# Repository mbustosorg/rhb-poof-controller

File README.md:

Red Hot Beverly Poof Controller
===============================

The Red Hot Beverly's poof button panel: CircuitPython on a Waveshare
ESP32-S3-POE-ETH at `192.168.1.15`, wired and powered over PoE.

1. Sends `/poof 1.0` on press and `/poof 0.0` on release to every listener.
2. Shows accumulator pressure (`/pressure`) on the left two digits.
3. Shows water bath temperature (`/temperature`) on the right two digits,
   blinking while `/water_heater` is 1.

OSC
---

| Direction | Address | Value | Producer / consumers |
| --- | --- | --- | --- |
| out | `/poof` | `1.0` pressed, `0.0` released | Every address in `CLIENTS`, including the body display |
| in | `/pressure` | psi, float | rhb-sensor-monitor |
| in | `/temperature` | degrees F, float | rhb-water-heater |
| in | `/water_heater` | `1.0` heating, `0.0` off | rhb-water-heater |

All on UDP 8888, except the body display at `192.168.1.3:10002`.

- `/poof` is a level, not a count: the release is sent three times, 50 ms
  apart, in case one is lost.
- At boot it sends `/poof 0.0`; a button held at power up must be released
  first.
- Edges are debounced 20 ms (`DEBOUNCE_MS`) and scanned in the background, so
  one that arrives during a send is late, not lost.
- An unreachable listener is skipped for 2, 4, 8 ... up to 60 s, since each
  failed send blocks for up to 0.5 s.
- A readout shows `--` before its first value and after 15 s without one.
  Values are rounded; above 99 shows `99`, below 0 shows `--`.

Hardware
--------

See [HARDWARE.md](HARDWARE.md) for the wiring and [kicad/](kicad/README.md) for the board.

| Part | ESP32-S3-ETH pin |
| --- | --- |
| HT16K33 display, I2C `0x70` | SDA IO39, SCL IO38 |
| Button, through a PC817 | IO40, internal pull-up, low = pressed |
| Onboard RGB LED | IO21, red while pressed |
| W5500 Ethernet | IO9-IO14, on the board |

The temperature pair blinks in software (`blink_loop`), since the HT16K33's
blink would flash all four digits.

`rhb_utils.py` and the OSC receive path (`poll_osc`, `start_osc`) are
rhb-water-heater's, with its W5500 fixes.  Keep the two in step.

Configuration
-------------

`config_rhb.json` is gitignored; copy `config_rhb.json.example`.

| Key | Default | Meaning |
| --- | --- | --- |
| `IP` | | Static address; no DHCP on the rig |
| `CLIENTS` | every rig listener | Who hears `/poof`.  `host` for port 8888, `host:port` otherwise |
| `POOF_PIN` | `"IO40"` | Button input, a `board` pin name |
| `DEBOUNCE_MS` | `20` | How long an edge must hold |
| `DISPLAY` | `112` (0x70) | Display I2C address, decimal since JSON has no hex |

Deploying
---------

Flash CircuitPython for the Waveshare ESP32-S3-ETH, then copy to `CIRCUITPY`
over USB-C:

- `code.py`, `rhb_utils.py`, `config_rhb.json`
- Into `lib/`, from the Adafruit bundle: `adafruit_ht16k33`,
  `adafruit_bus_device`, `adafruit_wiznet5k`, `adafruit_ticks`, `asyncio`,
  and optionally `neopixel`
- `microosc`, from the Community bundle

Console: `/dev/cu.usbmodem<UID>` (`cu.*`, not `tty.*`).  The display flashes
`[[]]` until the link is up, then `-- --` until data arrives.

Testing
-------

`test_osc.py` sends random readings every 5 s and prints each `/poof`.  Run
it from an address in `CLIENTS`:

    python3 test_osc.py --ip 192.168.1.15

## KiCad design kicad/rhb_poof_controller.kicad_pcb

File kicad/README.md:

Poof Controller Board
=====================

Two layer, 74 x 43 mm carrier for the circuit in [HARDWARE.md](../HARDWARE.md).
Parts: [bom.csv](bom.csv).

- **U2** mounts top face up; its RJ45 / USB-C end overhangs the left edge by
  2 mm.
- **R1, D1 and U1** sit under U2, between its header rows.  Fit them
  before the sockets, and keep them under 4.5 mm tall.
- **J1** takes the button wire, after the inline fuse at the supply, and the
  supply's negative.
- The bottom ground pour leaves out the 12V side, J1, R1, D1 and the
  PC817's LED pins, except for a strip along U2's pin 1-20 row.

The U2 footprint comes from Waveshare's dimension drawing.  **Check it against
a real board before ordering**: lay the module on a 1:1 print and see that
pin 1 lands on the square pad.  Also check that R1, D1 and U1 clear the
W5500, TF slot and USB-C on the module's underside once it's in its sockets.

Regenerating
------------

Edit the scripts, not the KiCad files, then run `./build.sh`.  Routing needs
Java 17+ and `~/tools/freerouting-1.9.jar`.

Expected warnings:

| Warning | Why |
| --- | --- |
| `lib_symbol_issues` | Symbols live only in the schematic |
| `extra_footprint` | Mounting holes aren't in the schematic |
| `silk_edge_clearance` | U2's outline runs past the board edge |

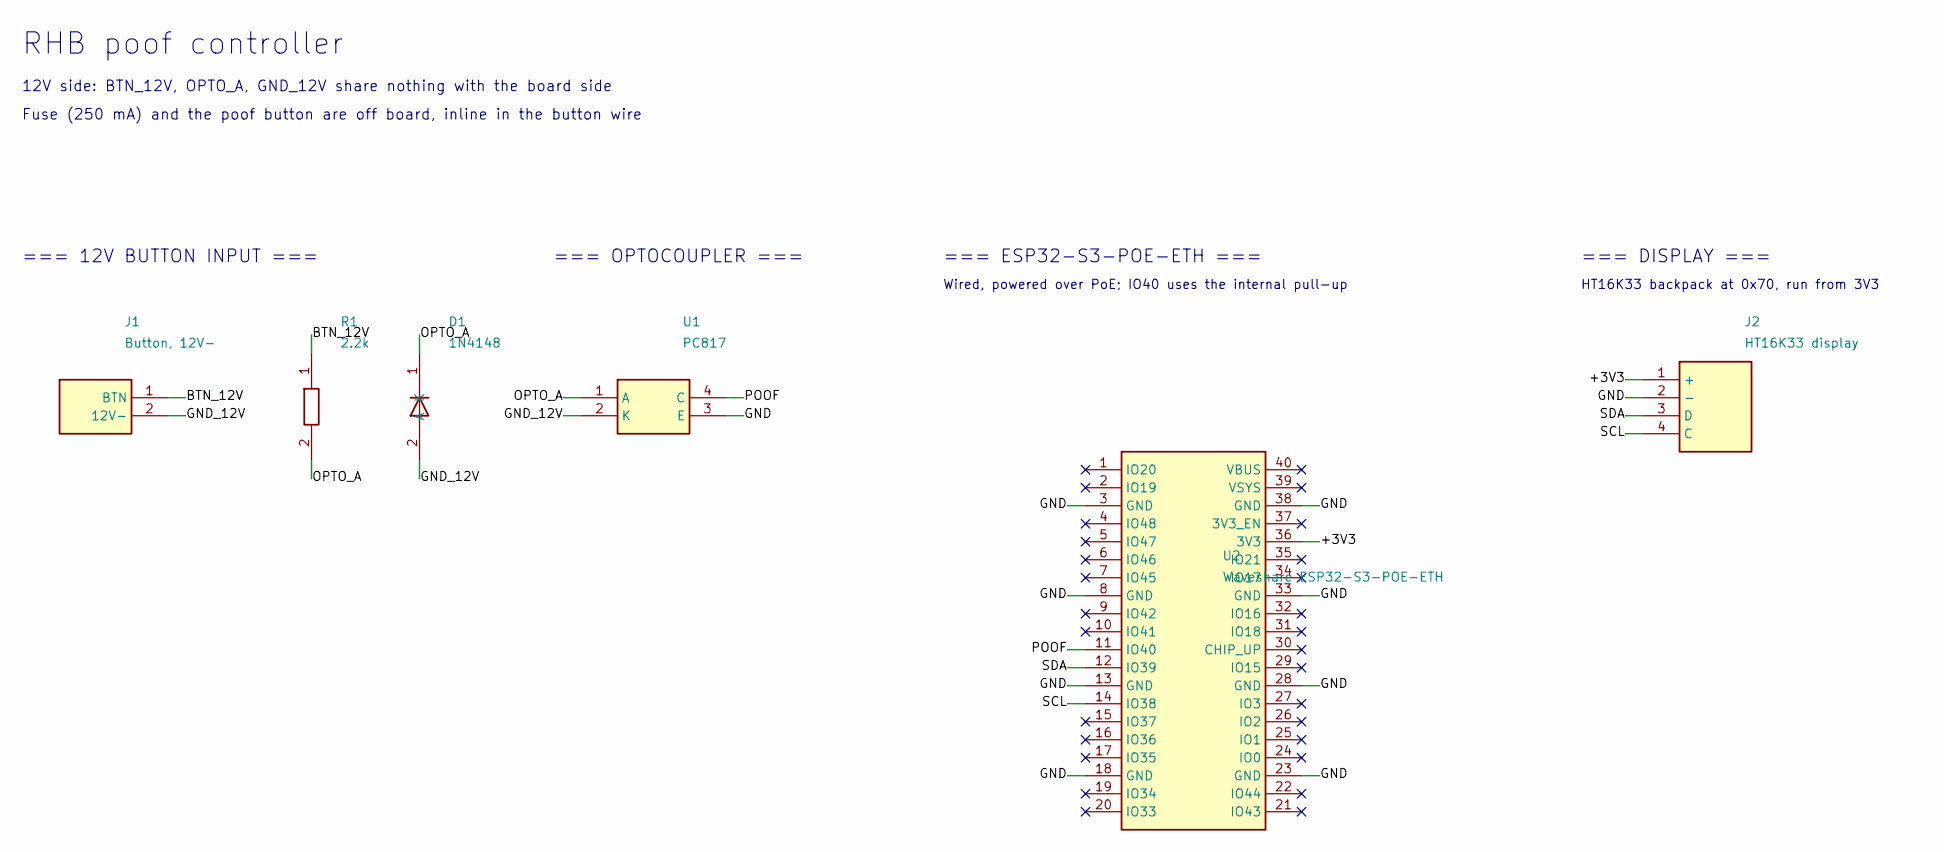
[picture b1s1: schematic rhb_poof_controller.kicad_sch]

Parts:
D1: 1N4148; D_DO-35_SOD27_P7.62mm_Horizontal
J1: Button, 12V-; TerminalBlock_Phoenix_MKDS-1,5-2-5.08_1x02_P5.08mm_Horizont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
J2: HT16K33 display; JST_XH_B4B-XH-A_1x04_P2.50mm_Vertical
R1: 2.2k; R_Axial_DIN0207_L6.3mm_D2.5mm_P10.16mm_Horizontal
U1: PC817; DIP-4_W7.62mm
U2: Waveshare ESP32-S3-POE-ETH; Waveshare_ESP32-S3-ETH

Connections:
/+3V3: J2.1 (+), U2.36 (3V3)
/BTN_12V: J1.1 (BTN), R1.1
/GND: J2.2 (-), U1.3 (E), U2.3 (GND), U2.8 (GND), U2.13 (GND), U2.18 (GND), U2.23 (GND), U2.28 (GND), U2.33 (GND), U2.38 (GND)
/GND_12V: D1.2 (A), J1.2 (12V-), U1.2 (K)
/OPTO_A: D1.1 (K), R1.2, U1.1 (A)
/POOF: U1.4 (C), U2.11 (IO40)
/SCL: J2.4 (C), U2.14 (IO38)
/SDA: J2.3 (D), U2.12 (IO39)

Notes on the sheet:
RHB poof controller
12V side: BTN_12V, OPTO_A, GND_12V share nothing with the board side
Fuse (250 mA) and the poof button are off board, inline in the button wire
=== 12V BUTTON INPUT ===
=== OPTOCOUPLER ===
=== ESP32-S3-POE-ETH ===
Wired, powered over PoE; IO40 uses the internal pull-up
=== DISPLAY ===
HT16K33 backpack at 0x70, run from 3V3

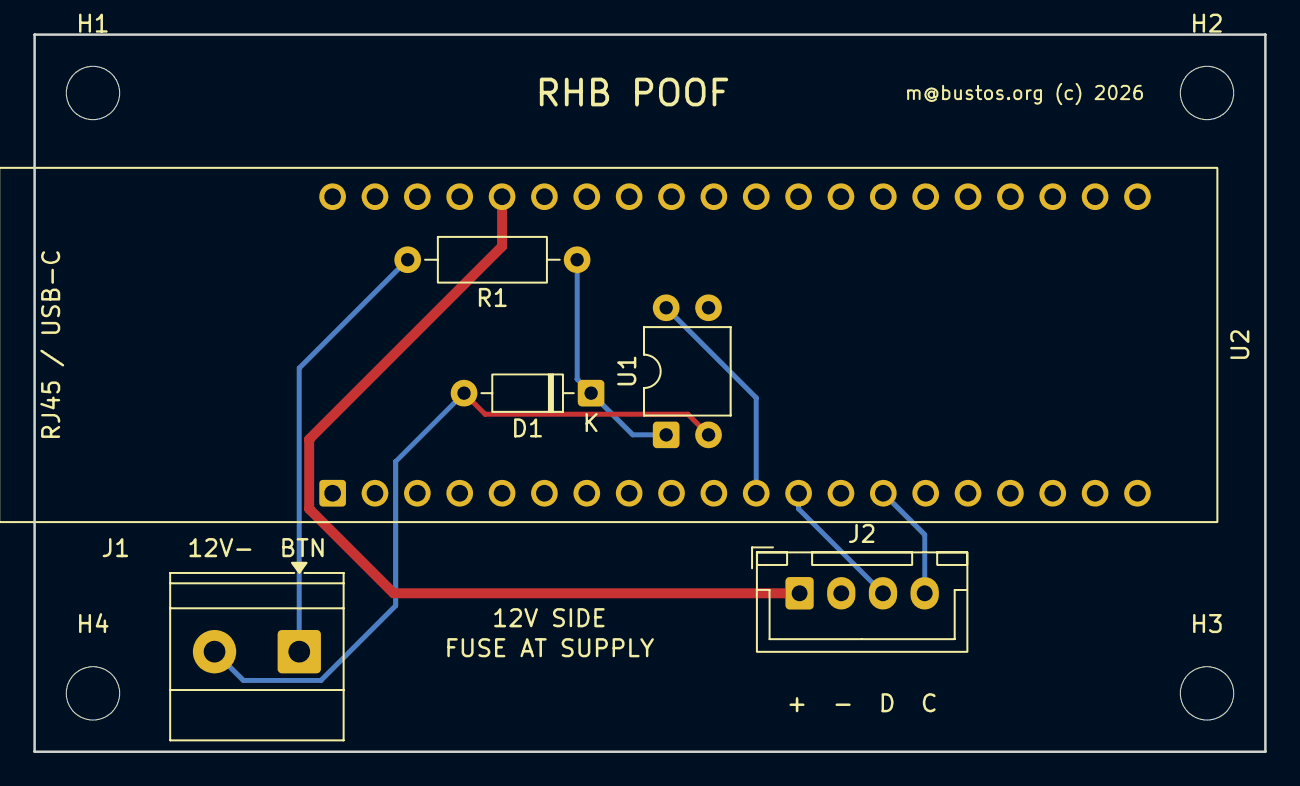
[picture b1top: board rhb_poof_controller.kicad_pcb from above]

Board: 2 copper layers, 73.8 x 43.0 mm, 10 parts (0 on the bottom side), 8 nets.

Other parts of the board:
H1, H2, H3, H4: M3; MountingHole_3.2mm_M3

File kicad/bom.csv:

Ref,Qty,Value,Description,Manufacturer,MPN,Notes
U2,1,ESP32-S3-POE-ETH,"ESP32-S3 module with W5500 Ethernet and PoE, Pico-style 2x20 header",Waveshare,ESP32-S3-POE-ETH,
,2,1x20 female,"Pin socket 1x20, 2.54 mm, through-hole (U2 sockets)",,,
U1,1,PC817,"Optocoupler, DIP-4",Sharp,PC817,
R1,1,2.2k,"Resistor, 1/4 W, axial",,,
D1,1,1N4148,"Signal diode, DO-35",,,
J1,1,Screw terminal 2 way,"Terminal block, 5.08 mm",Phoenix Contact,1715721,Button wire and 12V supply -
J2,1,JST-XH 4 pin,"Header, 2.50 mm, vertical",JST,B4B-XH-A(LF)(SN),To the HT16K33 display

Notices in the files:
kicad/rhb_poof_controller.kicad_pcb:
m@bustos.org (c) 2026
